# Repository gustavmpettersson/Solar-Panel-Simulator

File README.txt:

Solar Panel Simulator (SPS) for CubeSat testing

If you use any of this work, we ask that you cite the following individuals and provide a 
link to this repository:
Gustav M. Pettersson
Malte Gruber
Theodor-Adrian Stana
Sven Grahn
Christer Fuglesang
<https://github.com/gustavmpettersson/Solar-Panel-Simulator/>

This project is distributed in the hope that it will be useful, but WITHOUT ANY WARRANTY; 
without even the implied warranty of MERCHANTABILITY or FITNESS FOR A PARTICULAR PURPOSE. 
This should be considered EXPERIMENTAL RESEARCH technology and appropriate care should be 
taken. We will NOT be responsible for ANY related DAMAGES or ISSUES.

This work is Open Source Software and Hardware. See the two included <LICENSE.txt> files 
for details. The software is Copyright 2018 Gustav Pettersson, and released under the GNU 
General Public License. The hardware is Copyright 2018 Gustav Pettersson and Malte Gruber, 
and released under the CERN Open Hardware Licence.

In the root of this repository is a preprint of an article on the SPS submitted to Acta
Astronautica. It contains a lot of (hopefully) useful information on the system.

This system was designed by people working on the MIST and SEAM projects at the KTH Royal 
Institute of Technology.

We invite discussion, collaboration and help with implementing the system. Please contact 
us at <gupet@kth.se> or <gustavpettersson@live.com>.

HERE TO USE THE SPS? START BY READING <Introduction to the SPS>.

HERE TO BUILD THE SPS? HEAD INTO THE HARDWARE FOLDER FOR NECCESSARY FILES. THEN GO TO THE
<Building and Calibrating> FOLDER AND READ <Building Testing and Calibrating the SPS>.

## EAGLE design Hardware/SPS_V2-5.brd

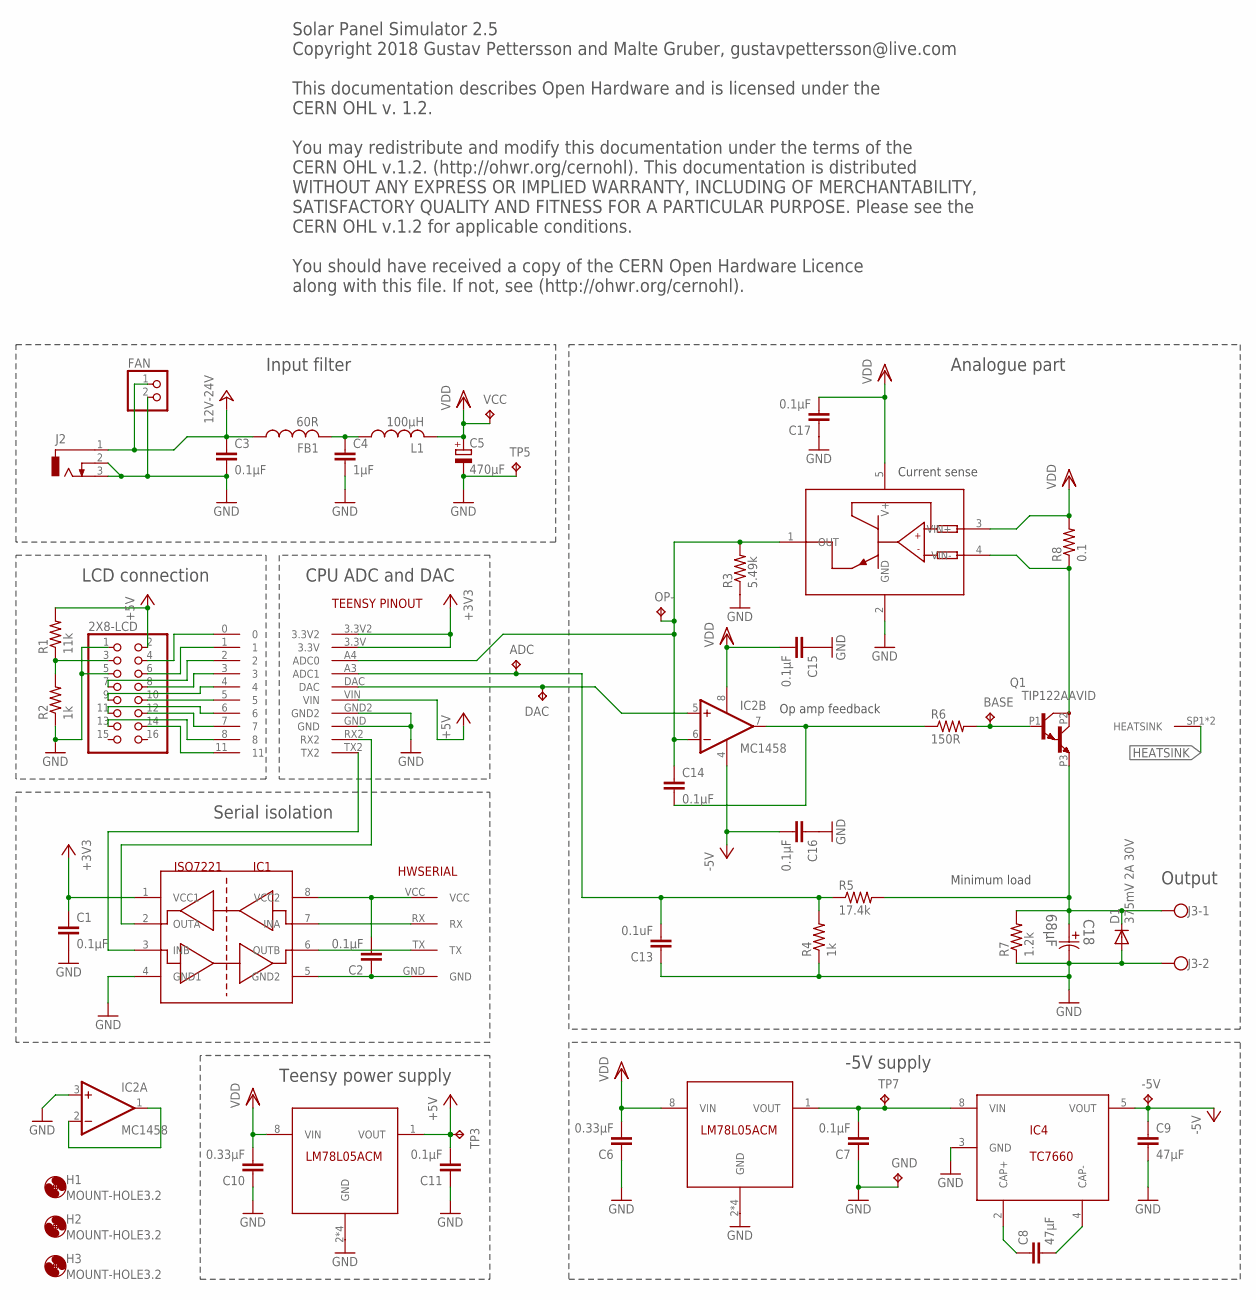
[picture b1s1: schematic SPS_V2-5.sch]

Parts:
2X8-LCD: PINHD-2X8; 2X08
-5V: TPTP10R; TP10R
ADC: TPTP10R; TP10R
BASE: TPTP10R; TP10R
C1, C2, C3, C7, C11, C14, C15, C16, C17: 0.1µF; C0603
C4: 1µF; C0603
C5: 470µF; 12.5MMSMD
C6, C10: 0.33µF; C0603
C8, C9: 47µF; C1206
C13: 0.1uF; C0603
C18: 68µF; CAPAE660X800N
D1: 375mV 2A 30V; DO214AC
DAC: TPTP10R; TP10R
DB1: TEENSY3.2
FAN: PINHD-1X2; 1X02
FB1: 60R; R1206
GND: TPTP10R; TP10R
H1, H2, H3: MOUNT-HOLE3.2; 3,2
IC1: ISO7221; SO8
IC2: MC1458; SO08
IC3, IC5: LM78L05ACM; SO8
IC4: TC7660; SO8
IC6: INA139; SOT23-5L
J1: HWSERIAL
J2: DCJ0303
J3: W237-102
L1: 100µH; 1210INDUCTOR
OP-: TPTP10R; TP10R
Q1: TIP122AAVID; OP-220-AAVID
R1: 11k; R0603
R2, R4: 1k; R0603
R3: 5.49k; R0603
R5: 17.4k; R0603
R6: 150R; R0603
R7: 1.2k; R1206
R8: 0.1; R1206
TP3, TP5, TP7: TPTP10R; TP10R
VCC: TPTP10R; TP10R

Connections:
+3V3: C1.1, DB1.3.3V, DB1.3.3V2, IC1.1 (VCC1)
+5V: 2X8-LCD.2, C11.2, DB1.VIN, IC5.1 (VOUT), R1.2, TP3.TP
+24V: C3.1, FAN.1, FB1.1, J2.1
-5V: -5V.TP, C9.1, C16.2, IC2.4 (V-), IC4.5 (VOUT)
GND: 2X8-LCD.1, 2X8-LCD.5, C1.2, C3.2, C4.2, C5.P$1 (-), C6.1, C7.1, C9.2, C10.1, C11.1, C13.1, C15.1, C16.1, C17.1, C18.2, D1.A, DB1.GND, DB1.GND2, FAN.2, GND.TP, IC1.4 (GND1), IC2.3 (+IN), IC3.2 (GND), IC3.3 (GND), IC3.6 (GND), IC3.7 (GND), IC4.3 (GND), IC5.2 (GND), IC5.3 (GND), IC5.6 (GND), IC5.7 (GND), IC6.2 (GND), J2.2, J2.3, J3.2, R2.1, R3.1, R4.1, R7.1, TP5.TP
HEATSINK: Q1.SP1 (HEATSINK), Q1.SP2 (HEATSINK)
unnamed: C14.2, IC2.7 (OUT), R6.1
unnamed: BASE.TP, Q1.P1 (B), R6.2
unnamed: C4.1, FB1.2, L1.P$1 (1)
unnamed: C14.1, DB1.A4 (ADC0), IC2.6 (-IN), IC6.1 (OUT), OP-.TP, R3.2
unnamed: C2.2, IC1.8 (VCC2), J1.VCC
unnamed: ADC.TP, C13.2, DB1.A3 (ADC1), R4.2, R5.1
unnamed: IC1.7 (INA), J1.RX
unnamed: DAC.TP, DB1.DAC, IC2.5 (+IN)
unnamed: 2X8-LCD.4, DB1.0
unnamed: IC6.4 (VIN-), Q1.P2 (C), R8.1
unnamed: IC1.6 (OUTB), J1.TX
unnamed: C8.2, IC4.4 (CAP-)
unnamed: C8.1, IC4.2 (CAP+)
unnamed: DB1.RX2, IC1.2 (OUTA)
unnamed: DB1.TX2, IC1.3 (INB)
unnamed: C2.1, IC1.5 (GND2), J1.GND
unnamed: C7.2, IC3.1 (VOUT), IC4.8 (VIN), TP7.TP
unnamed: 2X8-LCD.6, DB1.1
unnamed: 2X8-LCD.7, DB1.2
unnamed: 2X8-LCD.8, DB1.3
unnamed: 2X8-LCD.9, DB1.4
unnamed: 2X8-LCD.10, DB1.5
unnamed: 2X8-LCD.11, DB1.6
unnamed: 2X8-LCD.12, DB1.7
unnamed: 2X8-LCD.13, DB1.8
unnamed: 2X8-LCD.14, DB1.11
unnamed: 2X8-LCD.3, R1.1, R2.2
unnamed: IC2.1 (OUT), IC2.2 (-IN)
unnamed: C18.1, D1.C, J3.1, Q1.P3 (E), R5.2, R7.2
VDD: C5.P$2 (+), C6.2, C10.2, C15.2, C17.2, IC2.8 (V+), IC3.8 (VIN), IC5.8 (VIN), IC6.3 (VIN+), IC6.5 (V+), L1.P$2 (2), R8.2, VCC.TP

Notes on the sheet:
Teensy power supply
Serial isolation
-5V supply
Analogue part
Input filter
Current sense
Op amp feedback
Minimum load
Output
CPU ADC and DAC
LCD connection
Solar Panel Simulator 2.5 Copyright 2018 Gustav Pettersson and Malte Gruber, gustavpettersson@live.com This documentation describes Open Hardware and is licensed under the CERN OHL v. 1.2. You may redistribute and modify this documentation under the terms of the CERN OHL v.1.2. (http://ohwr.org/cer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

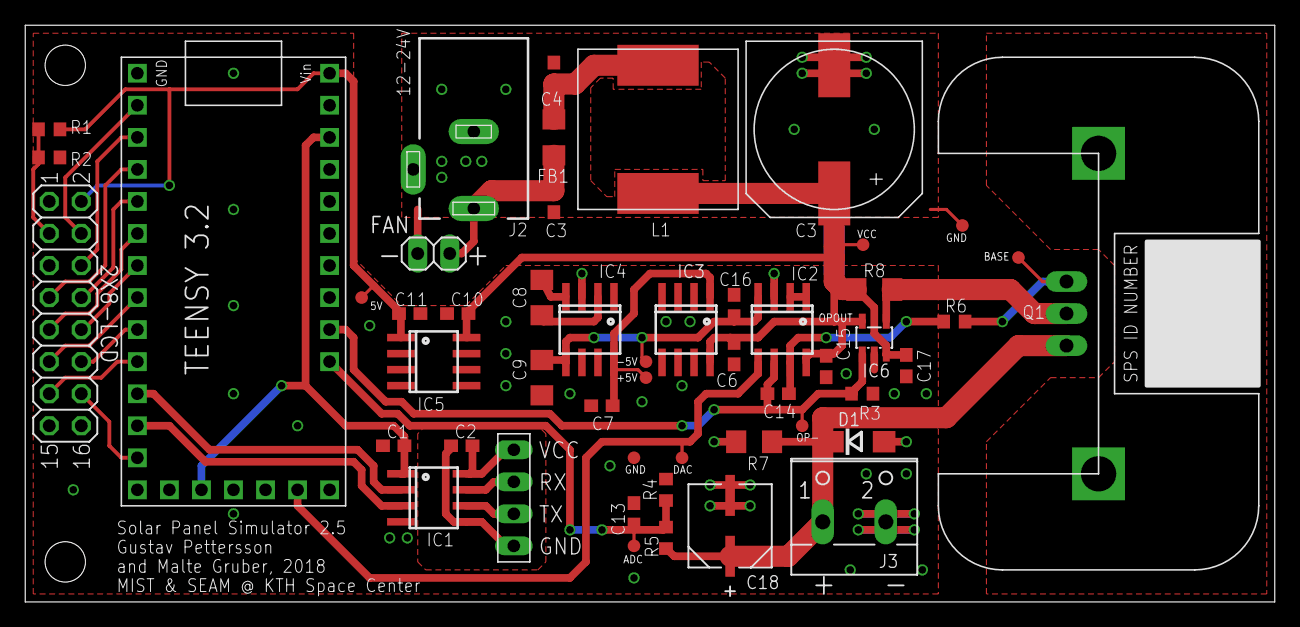
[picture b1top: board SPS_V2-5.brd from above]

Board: 2 copper layers, 99.1 x 45.7 mm, 54 parts (0 on the bottom side), 36 nets.

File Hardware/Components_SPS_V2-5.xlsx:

Type | Package | Farnell code | Pieces | Note | Components
0.1µF MLCC | 0603 | 2525112 | 11 |  | C1,2,3,7,11,13,14,15,16,17 |  | Don't mount C12
0.33µF MLCC | 0603 | 2346907 | 2 |  | C6,10
1µF MLCC | 0603 | 2346909 | 1 |  | C4
47µF MLCC | 1206 | 2426965 | 2 |  | C8,9
68µF Electrolytic | 8mm | 1539500 | 1 |  | C18
470µF Electrolytic | 12.5mm | 2079237 | 1 |  | C5
0.1R 1% | 1206 | 1107359 | 1 |  | R8
150R 1% | 0603 | 2447255 | 1 |  | R6
1k 1% | 0603 | 2447272 | 2 |  | R2,4
1.2k 0.5W | 1206 | 2331866 | 1 |  | R7
5.49k 1% | 0603 | 2670841 | 1 |  | R3
11k 1% | 0603 | 2447237 | 1 |  | R1
17.4k 1% | 0603 | 2670666 | 1 |  | R5
100µH MSS1210-104 | 1210 | 2288307 | 1 |  | L1
2A 375mV 30V Schottky | DO-214AC | 1467552 | 1 |  | D1
60R Ferrite bead | 1206 | 1651732 | 1 |  | FB1
LM78L05ACM | SO-8 | 2382979 | 2 |  | IC3,5
INA139 | SOT-23 | 1470398 | 1 |  | IC6
TC7660 | SO-8 | 1852313 | 1 |  | IC4
MC1458 | SO-8 | 9589821 | 1 |  | IC2
ISO7221A | SO-8 | 2764741 | 1 |  | IC1
TIP122 | TO220 | 9557881 | 1 |  | Q1
8x2 LCD |  | 2674124 | 1
20p 0.1" male |  | 1593423 | 2
4p 0.1" female |  | 1593460 | 1
8x2p 0.1" male |  | 1593445 | 1
5mm terminal block |  | 1716993 | 1
5.5/2.1mm DC Jack (10 pack) |  | 224959 | 1
AAVID Heatsink |  | 1213474 | 1
12V Fan | 40mm | 1012746 | 1 | for HC
24V Fan | 40mm | 1012748 | 1 | for HV
12V Power supply |  | 2708288 | 1 | for HC
24V Power supply |  | 2708291 | 1 | for HV
Mains cable |  | 1283799 | 1
USB cable |  | 2464950 | 1
Teensy 3.2 board |  | Mouser/PJRC | 1
M3 6mm (100 pack) |  | 1419986 | 4
M3 nut (100 pack) |  | 1420431 | 1
M3 20mm self tap (100 pack) |  | 2474974 | 2
M3 8mm standoff |  | 1466741 | 3

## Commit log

2018-01-15 minor updates
2018-01-15 Initial commit of IV curve algorithm
2018-01-16 added preprint of article
2018-01-17 Added user instructions
2019-01-22 SPSTeensy updated
    The SPSTeensy.ino file was updated to no longer rely on a large serial input buffer
2019-01-23 Fixed funtion call to start realtime GUI
2019-03-27 Added real-time infinite loop feature
    Realtime_SPS_GUI now has a third optional input 'restartAtEnd'. By passing 'true' here the real-time orbit playback will continue from the start instead of ending when the end of the orbit is reached
2019-03-27 Update SPSTeensy.ino
    Forbid hardware IDs 0 and 255 (possible defaults in the EEPROM memory)
